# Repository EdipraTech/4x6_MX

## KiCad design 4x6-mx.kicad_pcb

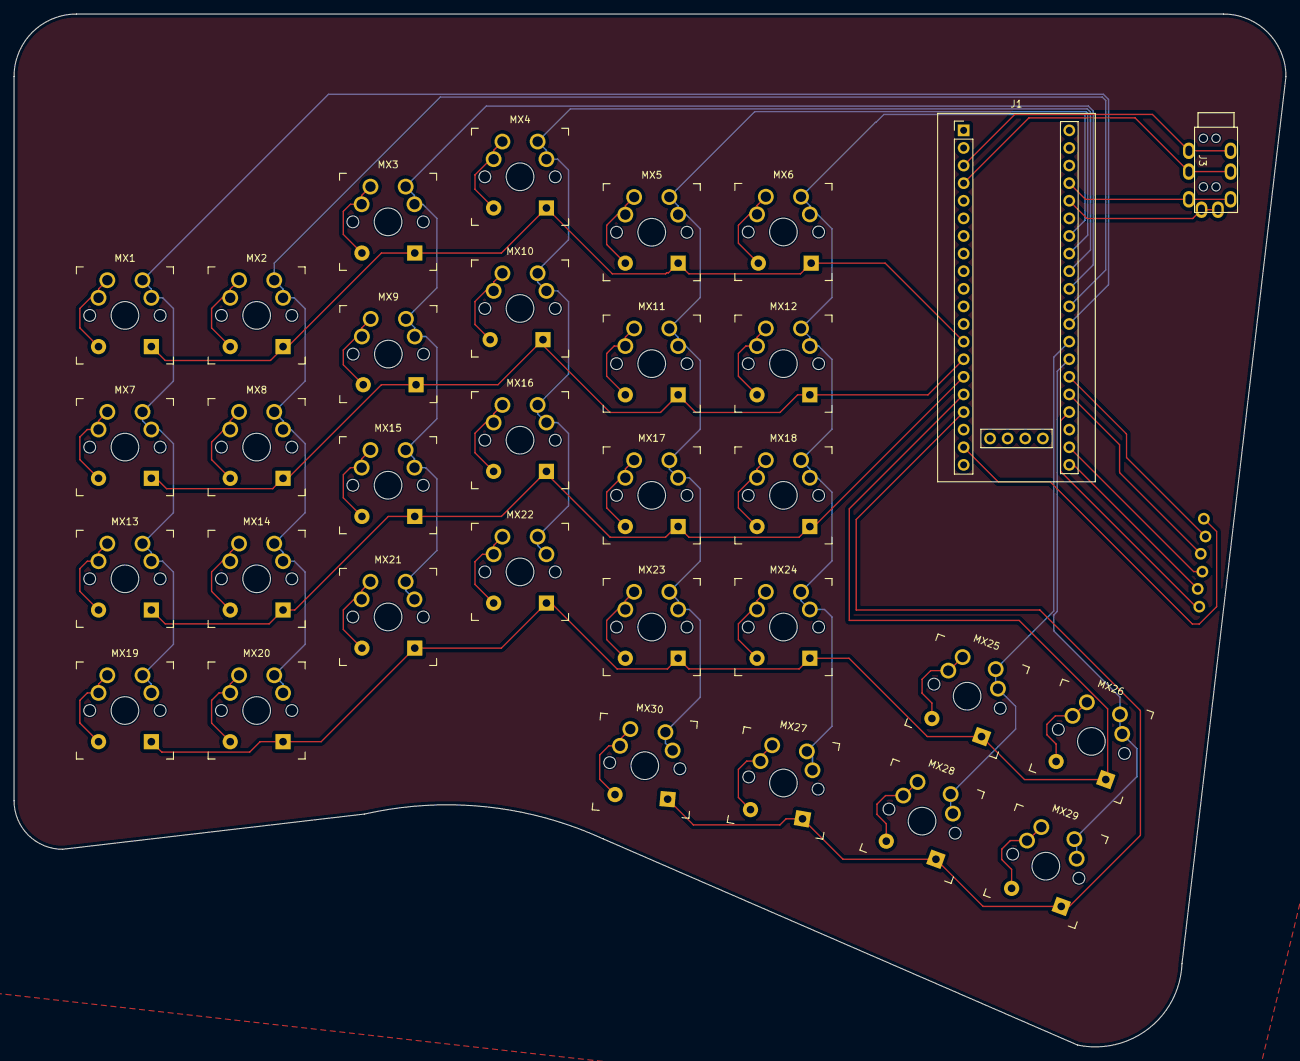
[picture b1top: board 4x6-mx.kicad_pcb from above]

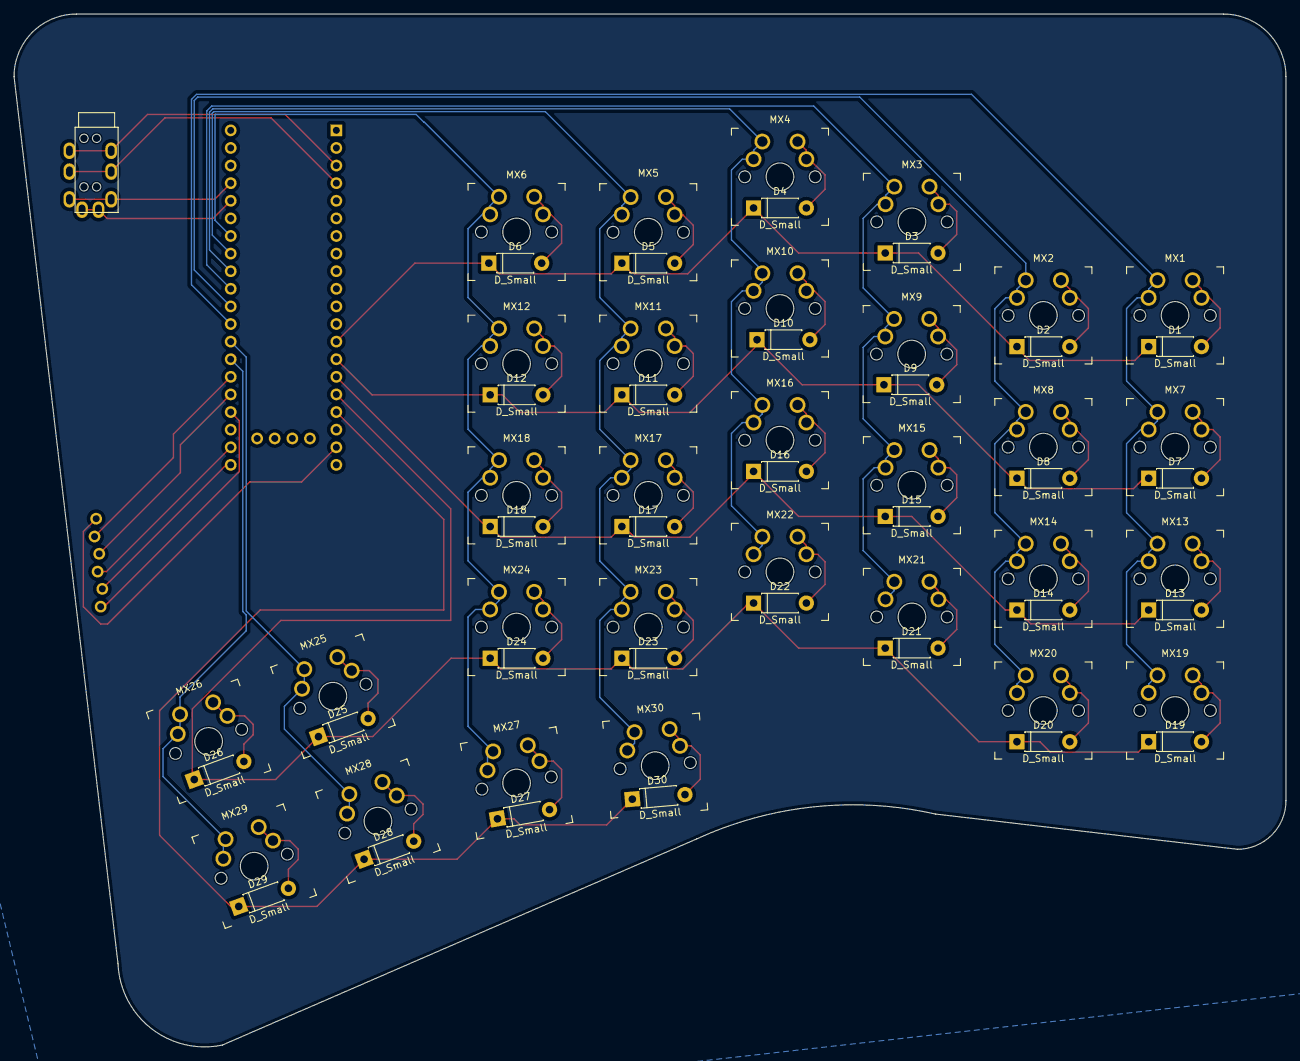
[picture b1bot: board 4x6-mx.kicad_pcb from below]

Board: 2 copper layers, 183.5 x 149.0 mm, 63 parts (60 on the bottom side), 53 nets.

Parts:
D1, D2, D3, D4, D5, D6, D7, D8, D9, D10, D11, D12, D13, D14, D15, D16, D17, D18, D19, D20, D21, D22, D23, D24, D25, D26, D27, D28, D29, D30: D_Small; D_DO-41_P7.62mm_Horizontal
J1: Conn_02x25_Counter_Clockwise; YAAJ_BluePill_SWD_2
J2: Conn_01x06; Header-6-Pin-ZigZag
J3: AudioJack4_Ground_SwitchTR1; CON_MJ-4PP-9_Reversible
MX1, MX2, MX3, MX4, MX5, MX6, MX7, MX8, MX9, MX10, MX11, MX12, MX13, MX14, MX15, MX16, MX17, MX18, MX19, MX20, MX21, MX22, MX23, MX24, MX25, MX26, MX27, MX28, MX29, MX30: MX_SW_solder; SW_MX_reversible

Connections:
5V: J1.24, J2.6
Column0: J1.29, MX1.1, MX7.1, MX13.1, MX19.1
Column1: J1.30, MX2.1, MX8.1, MX14.1, MX20.1
Column2: J1.31, MX3.1, MX9.1, MX15.1, MX21.1
Column3: J1.32, MX4.1, MX10.1, MX16.1, MX22.1
Column4: J1.33, MX5.1, MX11.1, MX17.1, MX23.1, MX30.1
Column5: J1.34, MX6.1, MX12.1, MX18.1, MX24.1, MX27.1
Column6: J1.28, MX25.1, MX28.1
Column7: J1.27, MX26.1, MX29.1
GND: J1.19, J2.1
MISO: J1.26, J2.2
MOSI: J1.22, J2.4
NCS: J1.21, J2.5
unnamed: D1.2 (A), MX1.2
unnamed: D2.2 (A), MX2.2
unnamed: D3.2 (A), MX3.2
unnamed: D4.2 (A), MX4.2
unnamed: D5.2 (A), MX5.2
unnamed: D6.2 (A), MX6.2
unnamed: D7.2 (A), MX7.2
unnamed: D8.2 (A), MX8.2
unnamed: D9.2 (A), MX9.2
unnamed: D10.2 (A), MX10.2
unnamed: D11.2 (A), MX11.2
unnamed: D12.2 (A), MX12.2
unnamed: D13.2 (A), MX13.2
unnamed: D14.2 (A), MX14.2
unnamed: D15.2 (A), MX15.2
unnamed: D16.2 (A), MX16.2
unnamed: D17.2 (A), MX17.2
unnamed: D18.2 (A), MX18.2
unnamed: D19.2 (A), MX19.2
unnamed: D20.2 (A), MX20.2
unnamed: D21.2 (A), MX21.2
unnamed: D22.2 (A), MX22.2
unnamed: D23.2 (A), MX23.2
unnamed: D24.2 (A), MX24.2
unnamed: D25.2 (A), MX25.2
unnamed: D26.2 (A), MX26.2
unnamed: D27.2 (A), MX27.2
unnamed: D28.2 (A), MX28.2
unnamed: D29.2 (A), MX29.2
unnamed: D30.2 (A), MX30.2
Row0: D1.1 (K), D2.1 (K), D3.1 (K), D4.1 (K), D5.1 (K), D6.1 (K), J1.13
Row1: D7.1 (K), D8.1 (K), D9.1 (K), D10.1 (K), D11.1 (K), D12.1 (K), J1.14
Row2: D13.1 (K), D14.1 (K), D15.1 (K), D16.1 (K), D17.1 (K), D18.1 (K), J1.15
Row3: D19.1 (K), D20.1 (K), D21.1 (K), D22.1 (K), D23.1 (K), D24.1 (K), D25.1 (K), D26.1 (K), J1.16
Row4: D27.1 (K), D28.1 (K), D29.1 (K), D30.1 (K), J1.17
SCLK: J1.25, J2.3
TRRS-R1: J1.37, J3.R1
TRRS-R2: J1.4, J3.R2
TRRS-S: J1.3, J3.S
TRRS-T: J1.36, J3.T

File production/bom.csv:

Designator,Footprint,Quantity,Value,LCSC Part #
"D1, D10, D11, D12, D13, D14, D15, D16, D17, D18, D19, D2, D20, D21, D22, D23, D24, D25, D26, D27, D28, D29, D3, D30, D4, D5, D6, D7, D8, D9",D_DO-41_P7.62mm_Horizontal,30,D_Small,
J1,YAAJ_BluePill_SWD_2,1,Conn_02x25_Counter_Clockwise,
J2,Header-6-Pin-ZigZag,1,Conn_01x06,
J3,CON_MJ-4PP-9_Reversible,1,AudioJack4_Ground_SwitchTR1,
"MX1, MX10, MX11, MX12, MX13, MX14, MX15, MX16, MX17, MX18, MX19, MX2, MX20, MX21, MX22, MX23, MX24, MX25, MX26, MX27, MX28, MX29, MX3, MX30, MX4, MX5, MX6, MX7, MX8, MX9",SW_MX_reversible,30,MX_SW_solder,

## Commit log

2024-05-24 qmk firmware (not working)
2024-05-24 remove vscode files
2024-05-24 replaced files
2024-05-24 moving firmware
